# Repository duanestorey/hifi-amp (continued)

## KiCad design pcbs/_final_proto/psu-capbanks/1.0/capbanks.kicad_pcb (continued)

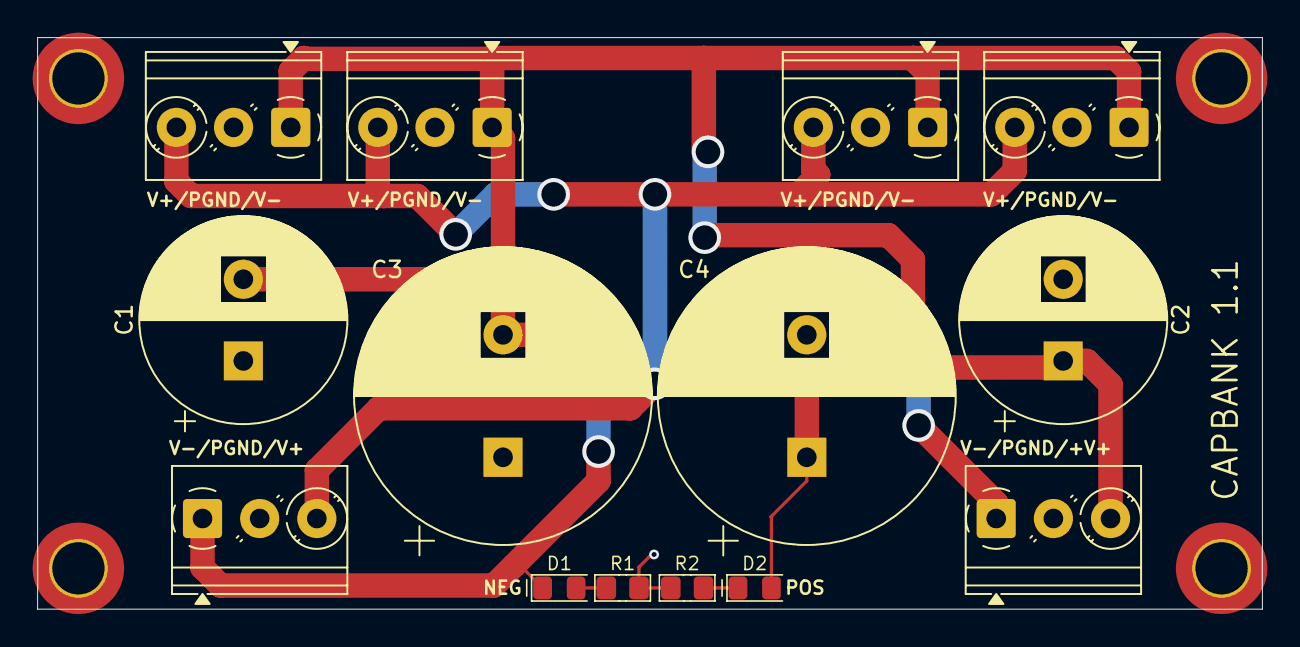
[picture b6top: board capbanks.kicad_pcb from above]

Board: 2 copper layers, 75.0 x 35.0 mm, 18 parts (0 on the bottom side), 5 nets.
